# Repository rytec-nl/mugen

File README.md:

# Mugen, my implementation

This project is born because I wanted to connect an external amplifier to my Samsung smart tv that fits my tv cabinet.
The obvious step was to build a hybrid tube/transistor amplifier myself. I was pointed to the Mugen hybrid amplifier. It fit my size and power requirements (I have 2 60W Visaton speakers). Altough there were some things that need to be added for it to work with my setup. 

For one i want to use my tv remote to change the volume, so I will need to implement a IR reciever that controls a variable resistor in the input signal. This means an additional power supply, a microcontroller to process the IR signals and control a digital potentiometer. 

The next challenge is that my TV only has an optical audio out, so I need to hook up a optical to aux convertor. My plan as of now is to buy the smallest I can find and build it into the amplifier. If this proves impossible, it will stay as an external box. 

Finally I want the amplifier to look good. So I am planning to change the design to have both tubes above eachother when facing the front of the amplifier. I can then place a see through window in front of the Tubes so they can be seen. Then hookup some LEDs to the microcontroller, and place them behind the tubes for some cool effects. Using the Microcontroller I can the dim the LEDs using a PWM signal. This all being carefull not to let the PWM signal interfere with the audio signal.

## Additions

As I'm working on the amplifier the design is improving. Instead of using plain windows in front of the tubes, the idea now is to use LCD displays where the backlight is removed. This gives a transparent view inside the amplifier when nothing is displayed. When needed lights inside the amp. will light up, and whatever is shown on the LCD becomes visible. This will be used for volume indication. 

In order for this to be implemented, in stead of simply adding a power supply to the main power board, a completely extra PCB will be added for the logic needed. 

## Todo

- [ ] Power Supply
   - [x] original schematic
   - [ ] schematic review 
   - [x] PCB
   - [ ] PCB review 
- [ ] Amplifier
   - [x] schematic 
   - [ ] schematic review
   - [ ] PCB
   - [ ] PCB review
- [ ] Logic board
   - [ ] schematic 
   - [ ] schematic review
   - [ ] PCB
   - [ ] PCB review
- [ ] Case
   - [ ] Front
      - [ ] design
      - [ ] build
   - [ ] back
      - [ ] design
      - [ ] build
   - [ ] bottom/top
   - [ ] sides
 - [ ] Firmware
    - [x] IR reciever test
    - [ ] IR reciever
    - [ ] Volume control
    - [ ] LED PWM
    - [ ] LED Level Control
    - [x] LCD control test
    - [ ] LCD control

## KiCad

The PCBs are designed using [KiCad](http://kicad.org/). This is the most usable free PCB design software I could find, that also works on Linux. Before this project I normally would use [Eagle](https://www.autodesk.com/products/eagle/overview), I even started this project using Eagle. But for me it is just to expensive for boards larger than `160mm x 100mm` ($65/month or in my case €85/month). So I chose a free alternative, that so far I am liking very much!

## Power Supply

### Schematic & PCB

### 3D View

## Amplifier

### Schematic & PCB

### 3D View

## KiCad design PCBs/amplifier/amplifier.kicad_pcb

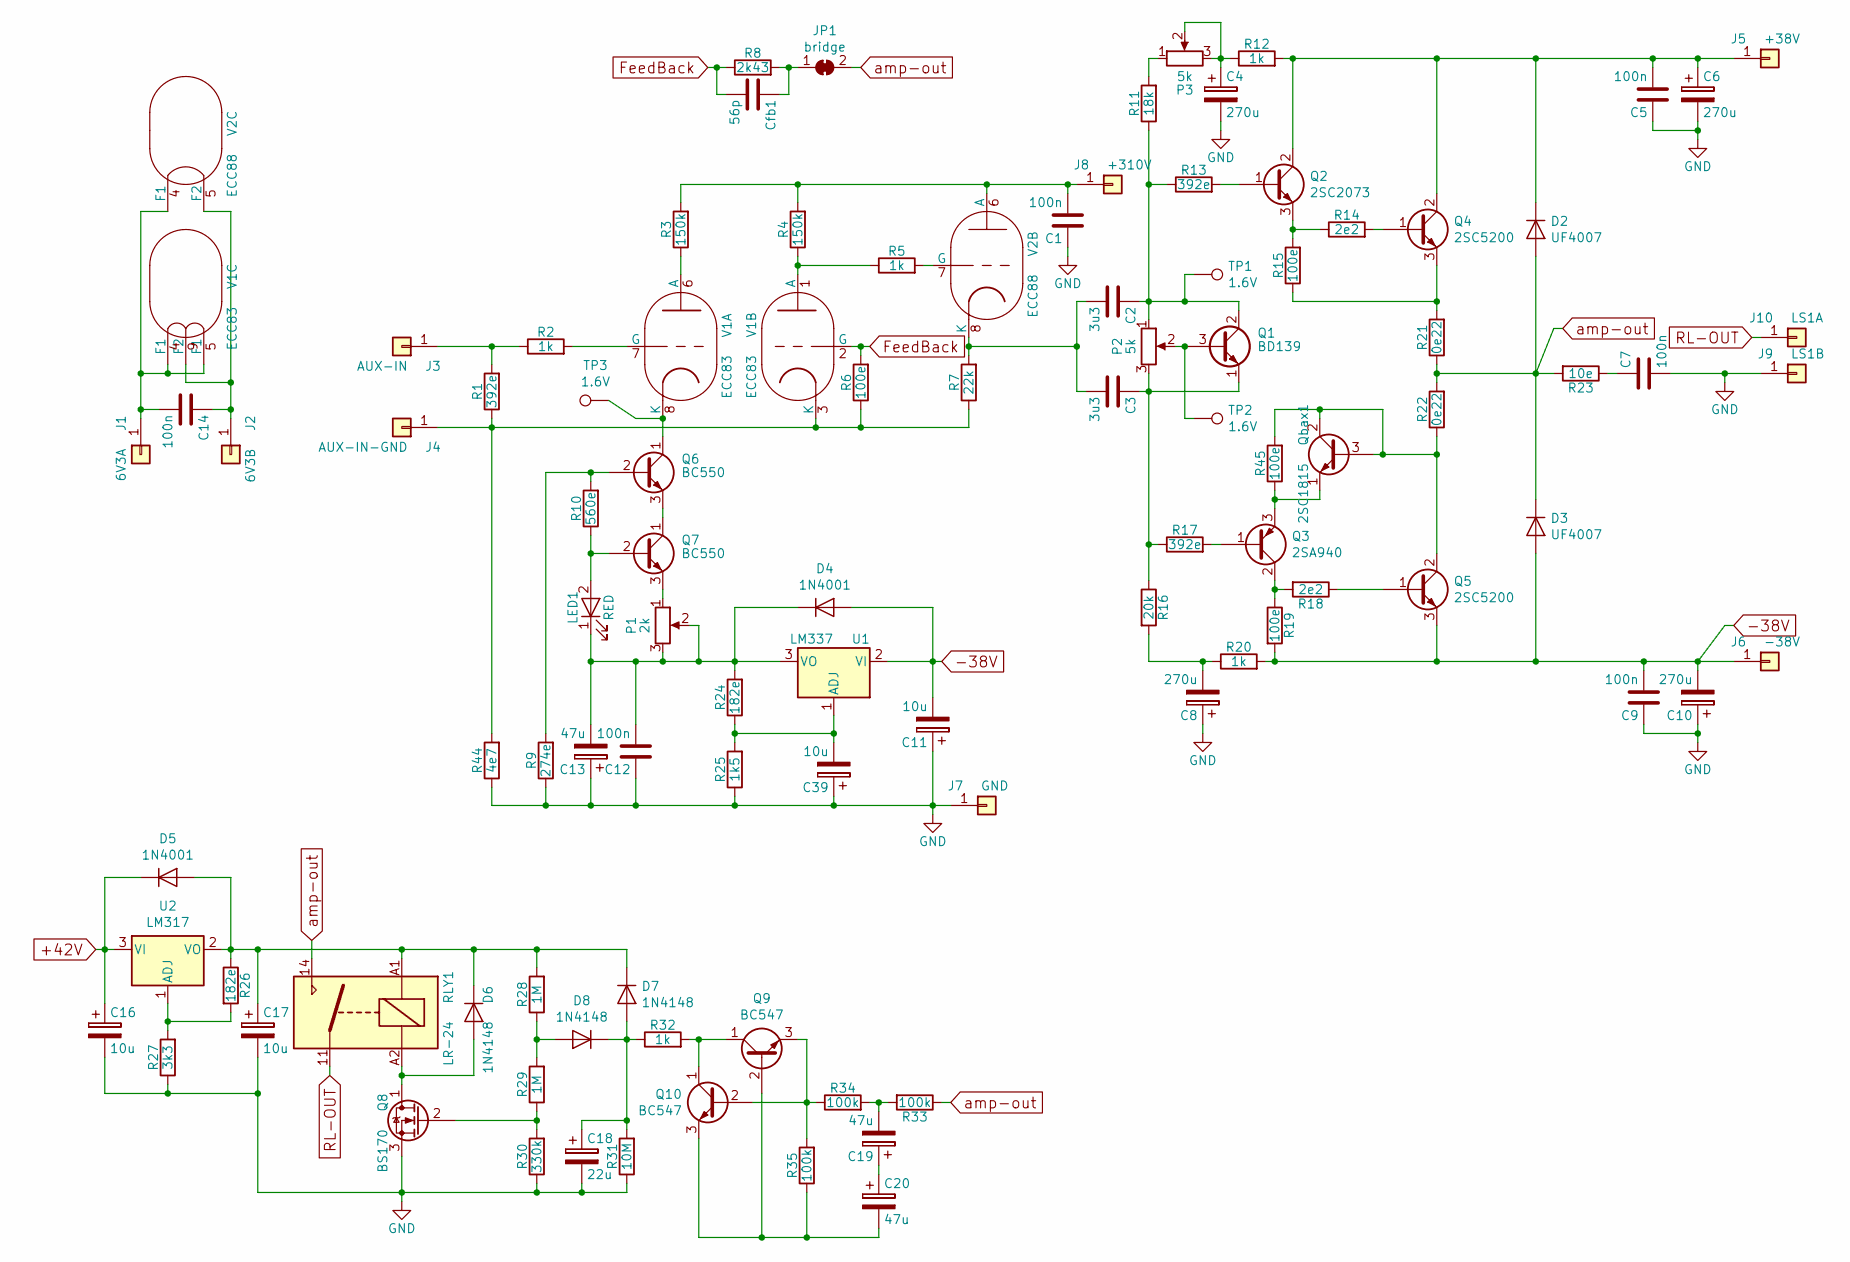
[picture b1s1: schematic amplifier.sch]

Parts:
C1: 100n; C_Rect_L16.5mm_W6.0mm_P15.00mm_MKT
C2, C3: 3u3; C_Rect_L41.5mm_W24.0mm_P37.50mm_MKS4
C4, C6, C8, C10: 270u; CP_Radial_D10.0mm_P3.80mm
C5, C9, C12, C14: 100n; C_Rect_L9.0mm_W3.8mm_P7.50mm_MKT
C7: 100n; C_Rect_L7.2mm_W5.5mm_P5.00mm_FKS2_FKP2_MKS2_MKP2
C11, C16, C17: 10u; CP_Radial_D6.3mm_P2.50mm
C13, C19, C20: 47u; CP_Radial_D10.0mm_P5.00mm
C18: 22u; CP_Radial_D6.3mm_P2.50mm
C39: 10u; CP_Radial_D5.0mm_P2.00mm
Cfb1: 56p; C_Disc_D5.0mm_W2.5mm_P2.50mm
D2, D3: UF4007; D_DO-41_SOD81_P10.16mm_Horizontal
D4, D5: 1N4001; D_DO-41_SOD81_P10.16mm_Horizontal
D6, D7, D8: 1N4148; D_DO-35_SOD27_P7.62mm_Horizontal
J1: 6V3A; SolderWirePad_single_2mmDrill
J2: 6V3B; SolderWirePad_single_2mmDrill
J3: AUX-IN; SolderWirePad_single_2mmDrill
J4: AUX-IN-GND; SolderWirePad_single_2mmDrill
J5: +38V; SolderWirePad_single_2mmDrill
J6: -38V; SolderWirePad_single_2mmDrill
J7: GND; SolderWirePad_single_2mmDrill
J8: +310V; SolderWirePad_single_2mmDrill
J9: LS1B; SolderWirePad_single_2mmDrill
J10: LS1A; SolderWirePad_single_2mmDrill
JP1: bridge; SolderJumper-2_P1.3mm_Bridged_RoundedPad1.0x1.5mm
LED1: RED; LED_D3.0mm
P1: 2k; Potentiometer_Bourns_3266Y_Vertical
P2, P3: 5k; Potentiometer_Bourns_3266Y_Vertical
Q1: BD139; TO-126_Vertical
Q2: 2SC2073; TO-220-3_Vertical
Q3: 2SA940; TO-220-3_Vertical
Q4, Q5: 2SC5200; TO-264_Vertical
Q6, Q7: BC550; TO-92
Q8: BS170; TO-92_Inline
Q9, Q10: BC547; TO-92
Qbax1: 2SC1815; TO-92
R1, R13, R17: 392e; R_Axial_DIN0207_L6.3mm_D2.5mm_P7.62mm_Horizontal
R2, R5, R12, R20, R32: 1k; R_Axial_DIN0207_L6.3mm_D2.5mm_P7.62mm_Horizontal
R3, R4: 150k; R_Axial_DIN0414_L11.9mm_D4.5mm_P15.24mm_Horizontal
R6, R15, R19, R45: 100e; R_Axial_DIN0207_L6.3mm_D2.5mm_P7.62mm_Horizontal
R7: 22k; R_Axial_DIN0414_L11.9mm_D4.5mm_P15.24mm_Horizontal
R8: 2k43; R_Axial_DIN0207_L6.3mm_D2.5mm_P7.62mm_Horizontal
R9: 274e; R_Axial_DIN0207_L6.3mm_D2.5mm_P7.62mm_Horizontal
R10: 560e; R_Axial_DIN0207_L6.3mm_D2.5mm_P7.62mm_Horizontal
R11: 18k; R_Axial_DIN0207_L6.3mm_D2.5mm_P7.62mm_Horizontal
R14, R18: 2e2; R_Axial_DIN0207_L6.3mm_D2.5mm_P7.62mm_Horizontal
R16: 20k; R_Axial_DIN0207_L6.3mm_D2.5mm_P7.62mm_Horizontal
R21, R22: 0e22; R_Axial_Power_L25.0mm_W9.0mm_P27.94mm
R23: 10e; R_Axial_DIN0414_L11.9mm_D4.5mm_P15.24mm_Horizontal
R24, R26: 182e; R_Axial_DIN0207_L6.3mm_D2.5mm_P7.62mm_Horizontal
R25: 1k5; R_Axial_DIN0207_L6.3mm_D2.5mm_P7.62mm_Horizontal
R27: 3k3; R_Axial_DIN0207_L6.3mm_D2.5mm_P7.62mm_Horizontal
R28, R29: 1M; R_Axial_DIN0207_L6.3mm_D2.5mm_P7.62mm_Horizontal
R30: 330k; R_Axial_DIN0207_L6.3mm_D2.5mm_P7.62mm_Horizontal
R31: 10M; R_Axial_DIN0207_L6.3mm_D2.5mm_P7.62mm_Horizontal
R33, R34, R35: 100k; R_Axial_DIN0207_L6.3mm_D2.5mm_P7.62mm_Horizontal
R44: 4e7; R_Axial_DIN0207_L6.3mm_D2.5mm_P7.62mm_Horizontal
RLY1: LR-24; Relay_SPST_Schrack-RP-II-1-16A-FormA_RM5mm
TP1, TP2, TP3: 1.6V; TestPoint_Pad_D1.0mm
U1: LM337; TO-220-3_Vertical
U2: LM317; TO-220-3_Vertical
V1: ECC83; Valve_ECC-83-2
V2: ECC88; Valve_ECC-83-2

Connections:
+42V: C16.1, D5.1 (K), U2.3 (VI)
-38V: C9.2, C10.2, C11.2, D3.2 (A), D4.2 (A), J6.1, Q5.3 (E), R19.2, R20.2, U1.2 (VI)
FeedBack: Cfb1.2, R6.2, R8.1, V1.2 (G)
GND: C1.1, C4.2, C5.1, C6.2, C7.2, C8.1, C9.1, C10.1, C11.1, C12.1, C13.1, C16.2, C17.2, C18.2, C39.1, J7.1, J9.1, Q8.3 (S), R9.1, R25.1, R27.1, R30.1, R31.1, R44.1
unnamed: C1.2, J8.1, R3.2, R4.2, V2.6 (A)
unnamed: C2.1, P2.1, Q1.2 (C), R11.1, R13.1, TP1.1
unnamed: C2.2, C3.2, R7.2, V2.8 (K)
unnamed: C3.1, P2.3, Q1.1 (E), R16.1, R17.1
unnamed: C4.1, P3.2, P3.3, R12.1
unnamed: C5.2, C6.1, D2.1 (K), J5.1, Q2.2 (C), Q4.2 (C), R12.2
unnamed: C7.1, R23.1
unnamed: C8.2, R16.2, R20.1
unnamed: C12.2, C13.2, D4.1 (K), LED1.1 (K), P1.2, P1.3, R24.2, U1.3 (VO)
unnamed: C14.1, J2.1, V1.9 (F2), V2.5 (F2)
unnamed: C14.2, J1.1, V1.4 (F1), V1.5 (F1), V2.4 (F1)
unnamed: C17.1, D5.2 (A), D6.1 (K), D7.1 (K), R26.1, R28.2, RLY1.A1, U2.2 (VO)
unnamed: C18.1, D7.2 (A), D8.1 (K), R31.2, R32.1
unnamed: C19.1, C20.1
unnamed: C19.2, R33.2, R34.2
unnamed: C20.2, Q9.2 (B), Q10.3 (E), R35.1
unnamed: C39.2, R24.1, R25.2, U1.1 (ADJ)
unnamed: Cfb1.1, JP1.1 (A), R8.2
unnamed: D6.2 (A), Q8.1 (D), RLY1.A2
unnamed: D8.2 (A), R28.1, R29.2
unnamed: J3.1, R1.2, R2.1
unnamed: J4.1, R1.1, R6.1, R7.1, R44.2, V1.3 (K)
unnamed: LED1.2 (A), Q7.2 (B), R10.1
unnamed: P1.1, Q7.3 (E)
unnamed: P2.2, Q1.3 (B), TP2.1
unnamed: P3.1, R11.2
unnamed: Q2.1 (B), R13.2
unnamed: Q2.3 (E), R14.1, R15.2
unnamed: Q3.1 (B), R17.2
unnamed: Q3.2 (C), R18.2, R19.1
unnamed: Q3.3 (E), Qbax1.1 (E), R45.1
unnamed: Q4.1 (B), R14.2
unnamed: Q4.3 (E), R15.1, R21.2
unnamed: Q5.1 (B), R18.1
unnamed: Q5.2 (C), Qbax1.2 (C), Qbax1.3 (B), R22.1, R45.2
unnamed: Q6.1 (C), TP3.1, V1.8 (K)
unnamed: Q6.2 (B), R9.2, R10.2
unnamed: Q6.3 (E), Q7.1 (C)
unnamed: Q8.2 (G), R29.1, R30.2
unnamed: Q9.1 (C), Q10.1 (C), R32.2
unnamed: Q9.3 (E), Q10.2 (B), R34.1, R35.2
unnamed: R2.2, V1.7 (G)
unnamed: R3.1, V1.6 (A)
unnamed: R4.1, R5.1, V1.1 (A)
unnamed: R5.2, V2.7 (G)
unnamed: R26.2, R27.2, U2.1 (ADJ)
RL-OUT: J10.1, RLY1.11
amp-out: D2.2 (A), D3.1 (K), JP1.2 (B), R21.1, R22.2, R23.2, R33.1, RLY1.14

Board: 2 copper layers, 99 parts (0 on the bottom side), 52 nets, no tracks yet.

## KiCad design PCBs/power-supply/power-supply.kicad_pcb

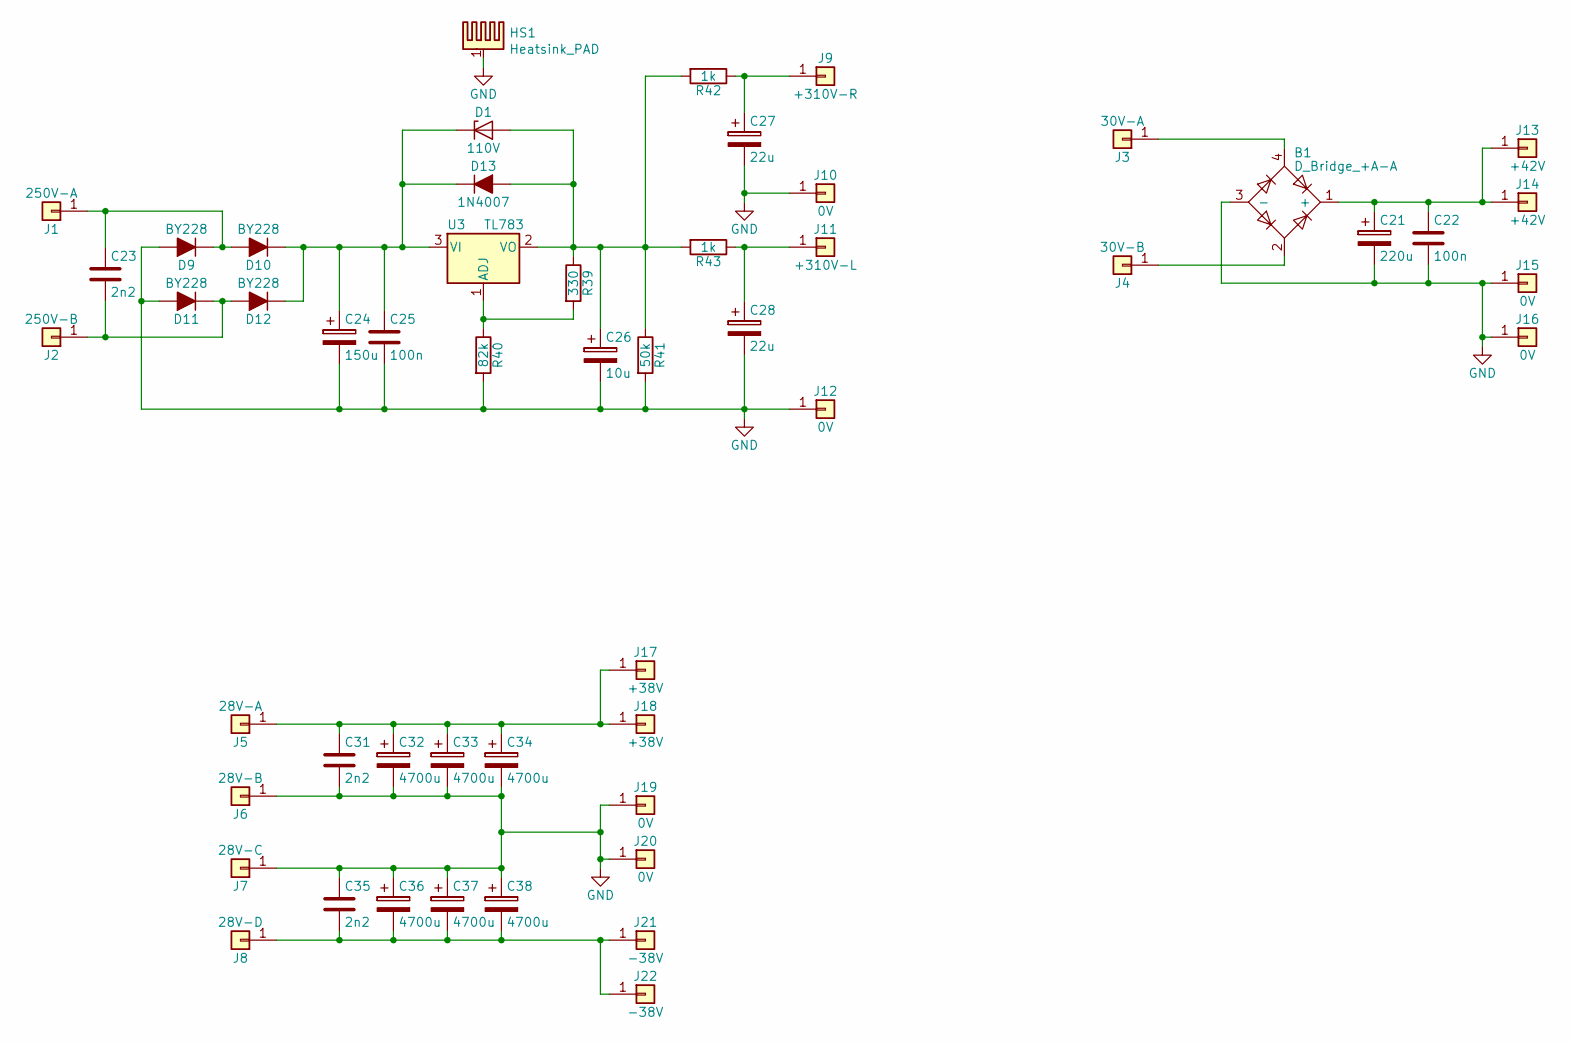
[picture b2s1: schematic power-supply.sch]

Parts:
B1: D_Bridge_+A-A; Diode_Bridge_Round_D9.8mm
C21: 220u; CP_Radial_D10.0mm_P3.80mm
C22: 100n; C_Rect_L4.6mm_W2.0mm_P2.50mm_MKS02_FKP02
C23: 2n2; C_Rect_L28.0mm_W8.0mm_P22.50mm_MKS4
C24: 150u; CP_Radial_D7.5mm_P2.50mm
C25: 100n; C_Rect_L18.0mm_W6.0mm_P15.00mm_FKS3_FKP3
C26: 10u; CP_Radial_D7.5mm_P2.50mm
C27, C28: 22u; CP_Radial_D13.0mm_P5.00mm
C31, C35: 2n2; C_Rect_L27.0mm_W9.0mm_P23.00mm
C32, C33, C34, C36, C37, C38: 4700u; CP_Radial_D35.0mm_P10.00mm_SnapIn
D1: 110V; D_DO-15_P10.16mm_Horizontal
D9, D10, D11, D12: BY228; D_T-1_P5.08mm_Horizontal
D13: 1N4007; D_DO-15_P10.16mm_Horizontal
HS1: Heatsink_PAD; Heatsink_Fischer_SK104-STC-STIC_35x13mm_2xDrill2.5mm
J1: 250V-A; SolderWirePad_single_2mmDrill
J2: 250V-B; SolderWirePad_single_2mmDrill
J3: 30V-A; SolderWirePad_single_2mmDrill
J4: 30V-B; SolderWirePad_single_2mmDrill
J5: 28V-A; SolderWirePad_single_2mmDrill
J6: 28V-B; SolderWirePad_single_2mmDrill
J7: 28V-C; SolderWirePad_single_2mmDrill
J8: 28V-D; SolderWirePad_single_2mmDrill
J9: +310V-R; SolderWirePad_single_2mmDrill
J10, J12, J15, J16, J19, J20: 0V; SolderWirePad_single_2mmDrill
J11: +310V-L; SolderWirePad_single_2mmDrill
J13, J14: +42V; SolderWirePad_single_2mmDrill
J17, J18: +38V; SolderWirePad_single_2mmDrill
J21, J22: -38V; SolderWirePad_single_2mmDrill
R39: 330; R_Axial_DIN0207_L6.3mm_D2.5mm_P10.16mm_Horizontal
R40: 82k; R_Axial_DIN0516_L15.5mm_D5.0mm_P20.32mm_Horizontal
R41: 50k; R_Axial_DIN0516_L15.5mm_D5.0mm_P20.32mm_Horizontal
R42, R43: 1k; R_Axial_DIN0414_L11.9mm_D4.5mm_P15.24mm_Horizontal
U3: TL783; TO-220-3_Vertical

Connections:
GND: B1.3 (-), C21.2, C22.2, C24.2, C25.2, C26.2, C27.2, C28.2, C31.2, C32.2, C33.2, C34.2, C35.1, C36.1, C37.1, C38.1, D9.2 (A), D11.2 (A), HS1.1, J6.1, J7.1, J10.1, J12.1, J15.1, J16.1, J19.1, J20.1, R40.2, R41.2
unnamed: B1.1 (+), C21.1, C22.1, J13.1, J14.1
unnamed: B1.2, J4.1
unnamed: B1.4, J3.1
unnamed: C23.1, D9.1 (K), D10.2 (A), J1.1
unnamed: C23.2, D11.1 (K), D12.2 (A), J2.1
unnamed: C24.1, C25.1, D1.1 (K), D10.1 (K), D12.1 (K), D13.1 (K), U3.3 (VI)
unnamed: C26.1, D1.2 (A), D13.2 (A), R39.1, R41.1, R42.2, R43.2, U3.2 (VO)
unnamed: C27.1, J9.1, R42.1
unnamed: C28.1, J11.1, R43.1
unnamed: C31.1, C32.1, C33.1, C34.1, J5.1, J17.1, J18.1
unnamed: C35.2, C36.2, C37.2, C38.2, J8.1, J21.1, J22.1
unnamed: R39.2, R40.1, U3.1 (ADJ)

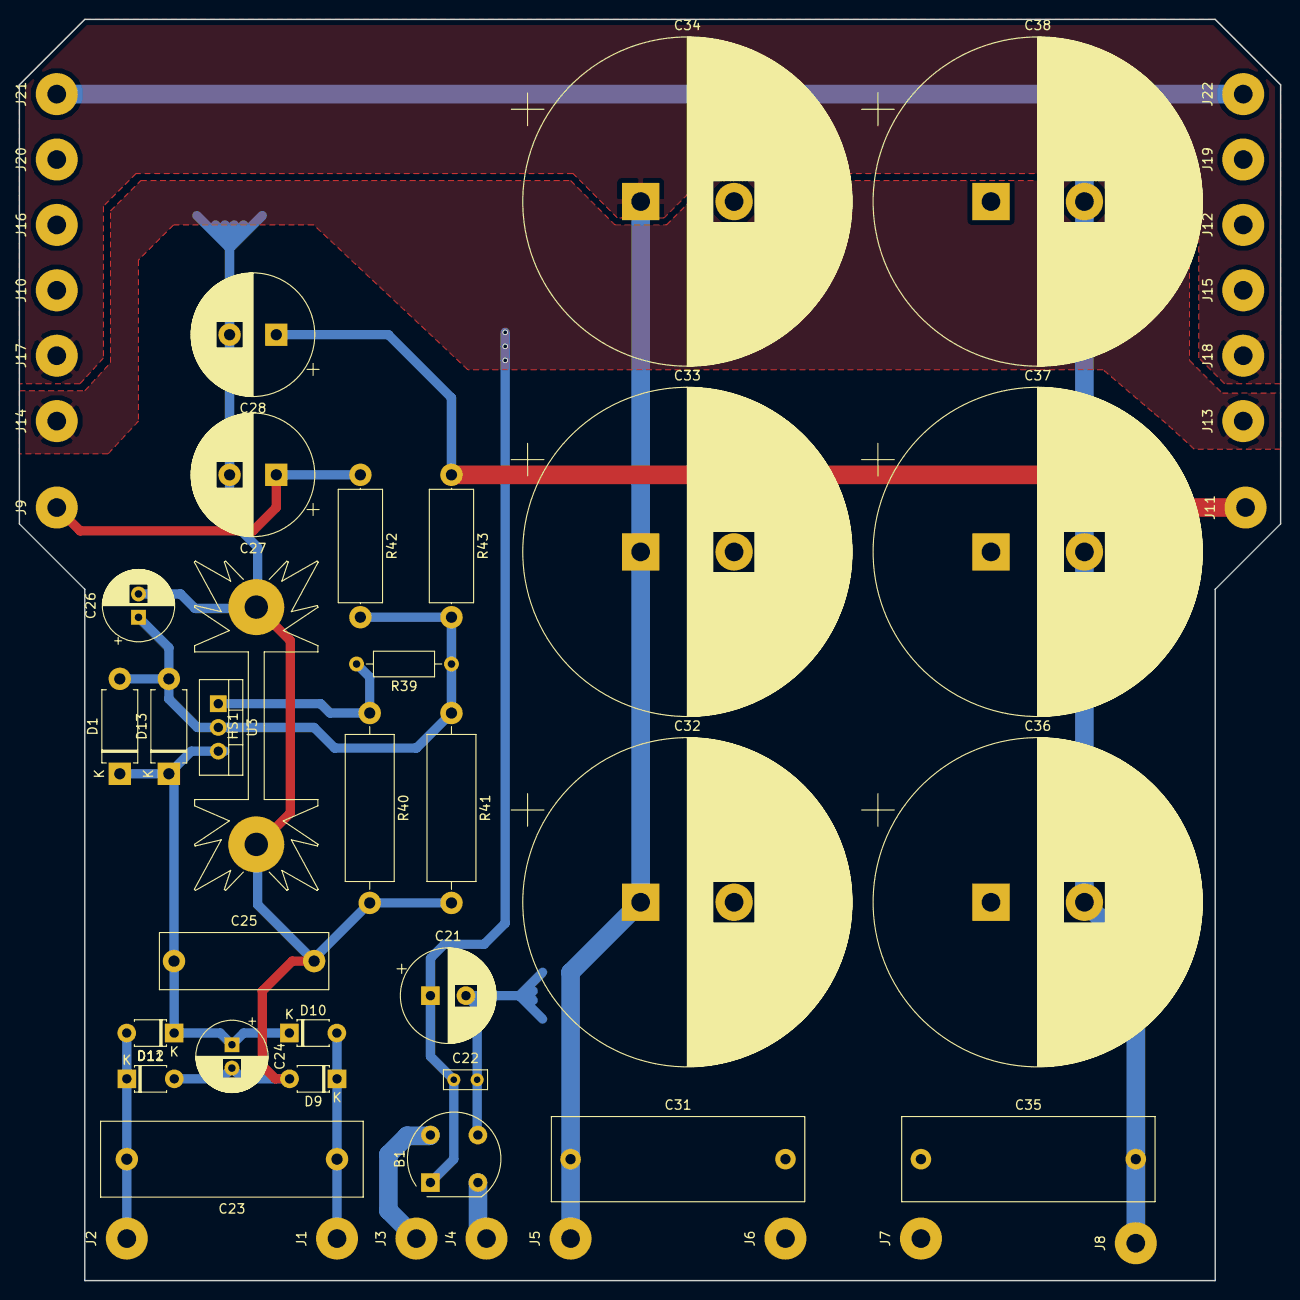
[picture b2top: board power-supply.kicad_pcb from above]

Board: 2 copper layers, 135.0 x 135.0 mm, 52 parts (0 on the bottom side), 13 nets.

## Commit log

2018-03-23 Initial commit.
2018-03-23 Added readme.
2018-03-23 added some structure.
2018-03-24 Started amp.
2018-03-24 Updated README.
2018-03-24 Basic design done.
2018-03-24 Added power supply image.
2018-03-27 Created kicad project.
2018-03-27 Started on power supply in kicad.
2018-03-28 First kicad version of power supply .
2018-03-29 Small change.
2018-04-02 Started on amplifier pcb .
2018-04-02 Added image.
2018-04-05 updated to kicad 5.
2018-04-06 Changed footprints to kicad 5 names.
2018-04-06 Updated 3D image with ray-tracing.
2018-04-13 fixed schematic.
2018-04-13 Raw finish of amp. schematic.
2018-04-13 Crude start of pcb.
2018-04-15 Fixed power-supply schematic.
2018-04-15 Added correct annotation and started assigning footprints.
2018-04-15 Updated PCB image.
2018-04-16 Updated amp. sch. image.
2018-04-17 amp. sch. done, all footprints added.
2018-04-19 Rough component placement amp. pcb.
2021-11-08 Update README.md
    https://forum.kicad.info/t/warning-avoid-all-links-to-kicad-pcb-org-use-kicad-org/31521
